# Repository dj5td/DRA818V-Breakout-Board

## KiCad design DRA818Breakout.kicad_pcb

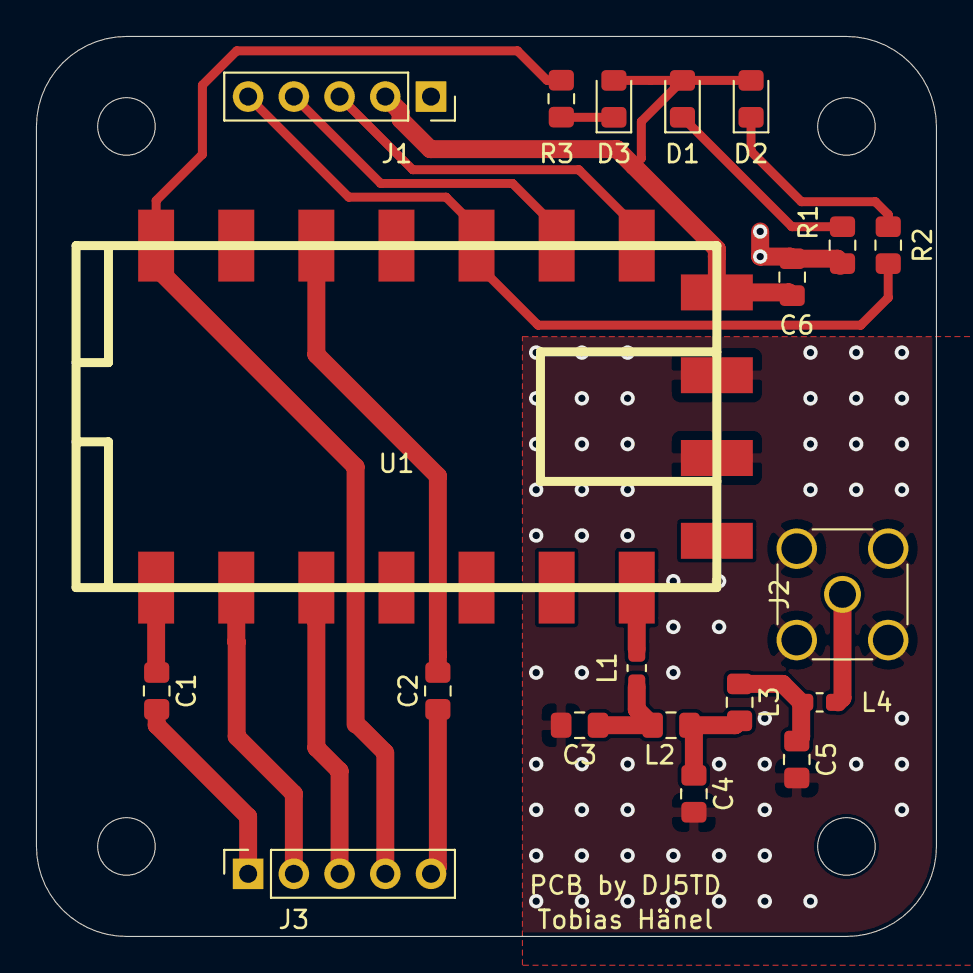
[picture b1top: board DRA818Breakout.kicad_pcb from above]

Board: 2 copper layers, 50.0 x 50.0 mm, 20 parts (0 on the bottom side), 20 nets.

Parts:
C1, C2: 100nF; C_0805_2012Metric_Pad1.15x1.40mm_HandSolder
C3, C5: 27pF; C_0805_2012Metric_Pad1.15x1.40mm_HandSolder
C4: 33pF; C_0805_2012Metric_Pad1.15x1.40mm_HandSolder
C6: 10 uF; C_0805_2012Metric_Pad1.15x1.40mm_HandSolder
D1, D2, D3: LED; LED_0805_2012Metric_Pad1.15x1.40mm_HandSolder
J1, J3: Conn_01x05_Male; PinSocket_1x05_P2.54mm_Vertical
J2: Conn_Coaxial; SMA_Amphenol_132291_Vertical
L1, L4: 62nH; L_0603_1608Metric_Pad1.05x0.95mm_HandSolder
L2, L3: 100nH; L_0805_2012Metric_Pad1.15x1.40mm_HandSolder
R1, R2, R3: 1KR; R_0805_2012Metric_Pad1.15x1.40mm_HandSolder
U1: DRA818V; DRA818U_handsolder

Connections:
GND: C3.2, C4.2, C5.2, C6.1, J1.1, J2.2, R1.1, U1.9, U1.10
unnamed: C1.1, U1.18
unnamed: C1.2, J3.1
unnamed: C2.1, J3.5
unnamed: C2.2, U1.3
unnamed: C3.1, L1.1, L2.2
unnamed: C4.1, L2.1, L3.2
unnamed: C5.1, L3.1, L4.2
unnamed: D1.1, R1.2
unnamed: D2.1, R2.2
unnamed: D3.1, R3.2
unnamed: J1.3, U1.7
unnamed: J1.4, U1.6
unnamed: J1.5, R2.1, U1.5
unnamed: J2.1, L4.1
unnamed: J3.2, U1.17
unnamed: J3.3, U1.16
unnamed: J3.4, R3.1, U1.1
unnamed: L1.2, U1.12
VCC: C6.2, D1.2, D2.2, D3.2, J1.2, U1.8
